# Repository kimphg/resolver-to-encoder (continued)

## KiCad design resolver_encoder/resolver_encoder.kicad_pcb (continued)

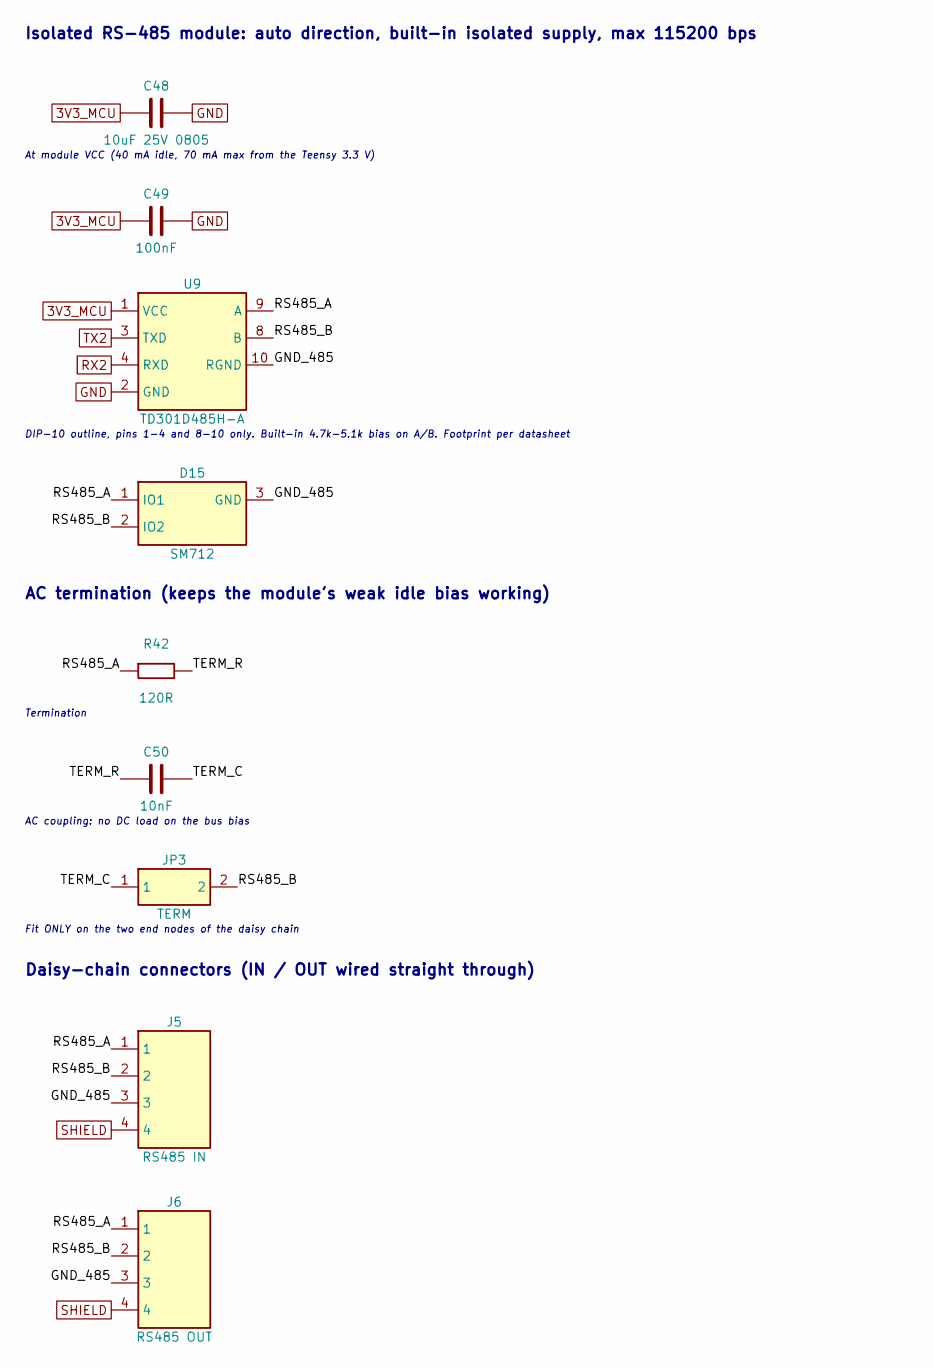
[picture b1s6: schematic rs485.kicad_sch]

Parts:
C48: 10uF 25V 0805; C_0805_2012Metric; MPN CL21A106KAYNNNE; LCSC C15850
C49: 100nF; C_0603_1608Metric; MPN CL10B104KB8NNNC; LCSC C1591
C50: 10nF; C_0603_1608Metric; MPN CL10B103KB8NNNC; LCSC C1589
D15: SM712; SOT-23; MPN SM712; LCSC C521963
J5: RS485 IN; PhoenixContact_MC_1,5_4-G-3.81_1x04_P3.81mm_Horizontal; MPN WJ15EDGRC-3.81-04P + plug WJ15EDGK-3.81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; LCSC C7245
J6: RS485 OUT; PhoenixContact_MC_1,5_4-G-3.81_1x04_P3.81mm_Horizontal; MPN WJ15EDGRC-3.81-04P + plug WJ15EDGK-3.81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; LCSC C7245
JP3: TERM; PinHeader_1x02_P2.54mm_Vertical; MPN 2.54 mm 1x40 header (cut) + jumper cap; LCSC C2337
R42: 120R; R_0805_2012Metric; MPN 0805W8F1200T5E; LCSC C17437
U9: TD301D485H-A; TD301D485H-A_DIP; MPN TD301D485H-A (YLPTEC); LCSC C2992416

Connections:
3V3_MCU: C48.1, C49.1, U9.1 (VCC); also elsewhere on the board
/RS485/GND_485: D15.3 (GND), J5.3, J6.3, U9.10 (RGND)
/RS485/RS485_A: D15.1 (IO1), J5.1, J6.1, R42.1, U9.9 (A)
/RS485/RS485_B: D15.2 (IO2), J5.2, J6.2, JP3.2, U9.8 (B)
/RS485/TERM_C: C50.2, JP3.1
/RS485/TERM_R: C50.1, R42.2
GND: C48.2, C49.2, U9.2 (GND); also elsewhere on the board
RX2: U9.4 (RXD); also elsewhere on the board
SHIELD: J5.4, J6.4; also elsewhere on the board
TX2: U9.3 (TXD); also elsewhere on the board

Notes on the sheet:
Isolated RS-485 module: auto direction, built-in isolated supply, max 115200 bps
At module VCC (40 mA idle, 70 mA max from the Teensy 3.3 V)
DIP-10 outline, pins 1-4 and 8-10 only. Built-in 4.7k-5.1k bias on A/B. Footprint per datasheet
AC termination (keeps the module's weak idle bias working)
Termination
AC coupling: no DC load on the bus bias
Fit ONLY on the two end nodes of the daisy chain
Daisy-chain connectors (IN / OUT wired straight through)

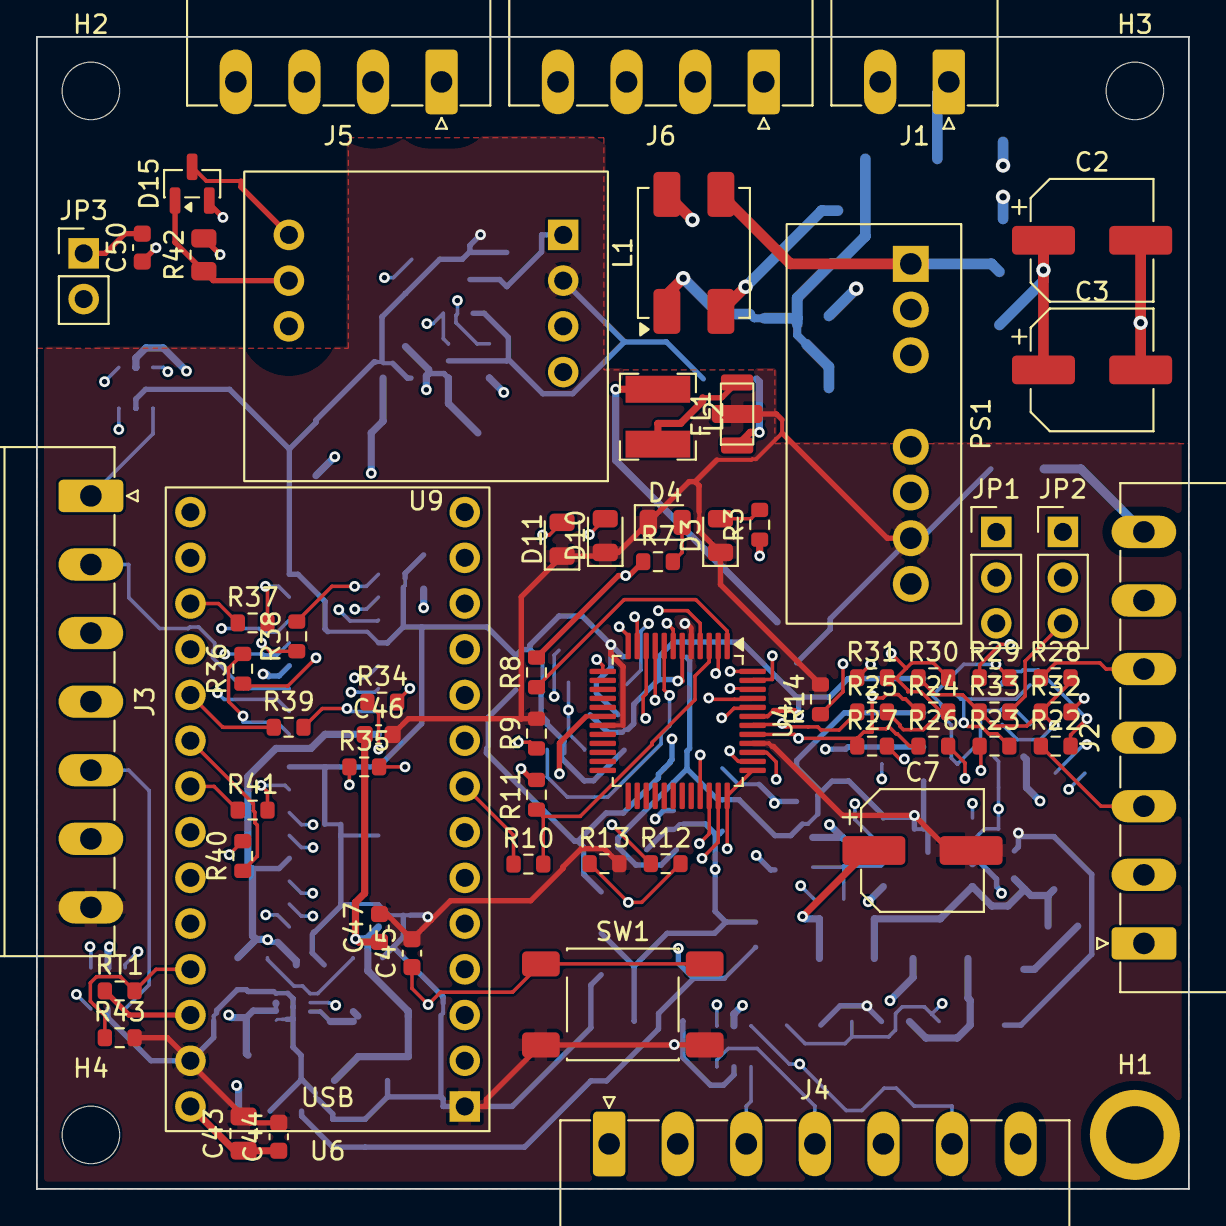
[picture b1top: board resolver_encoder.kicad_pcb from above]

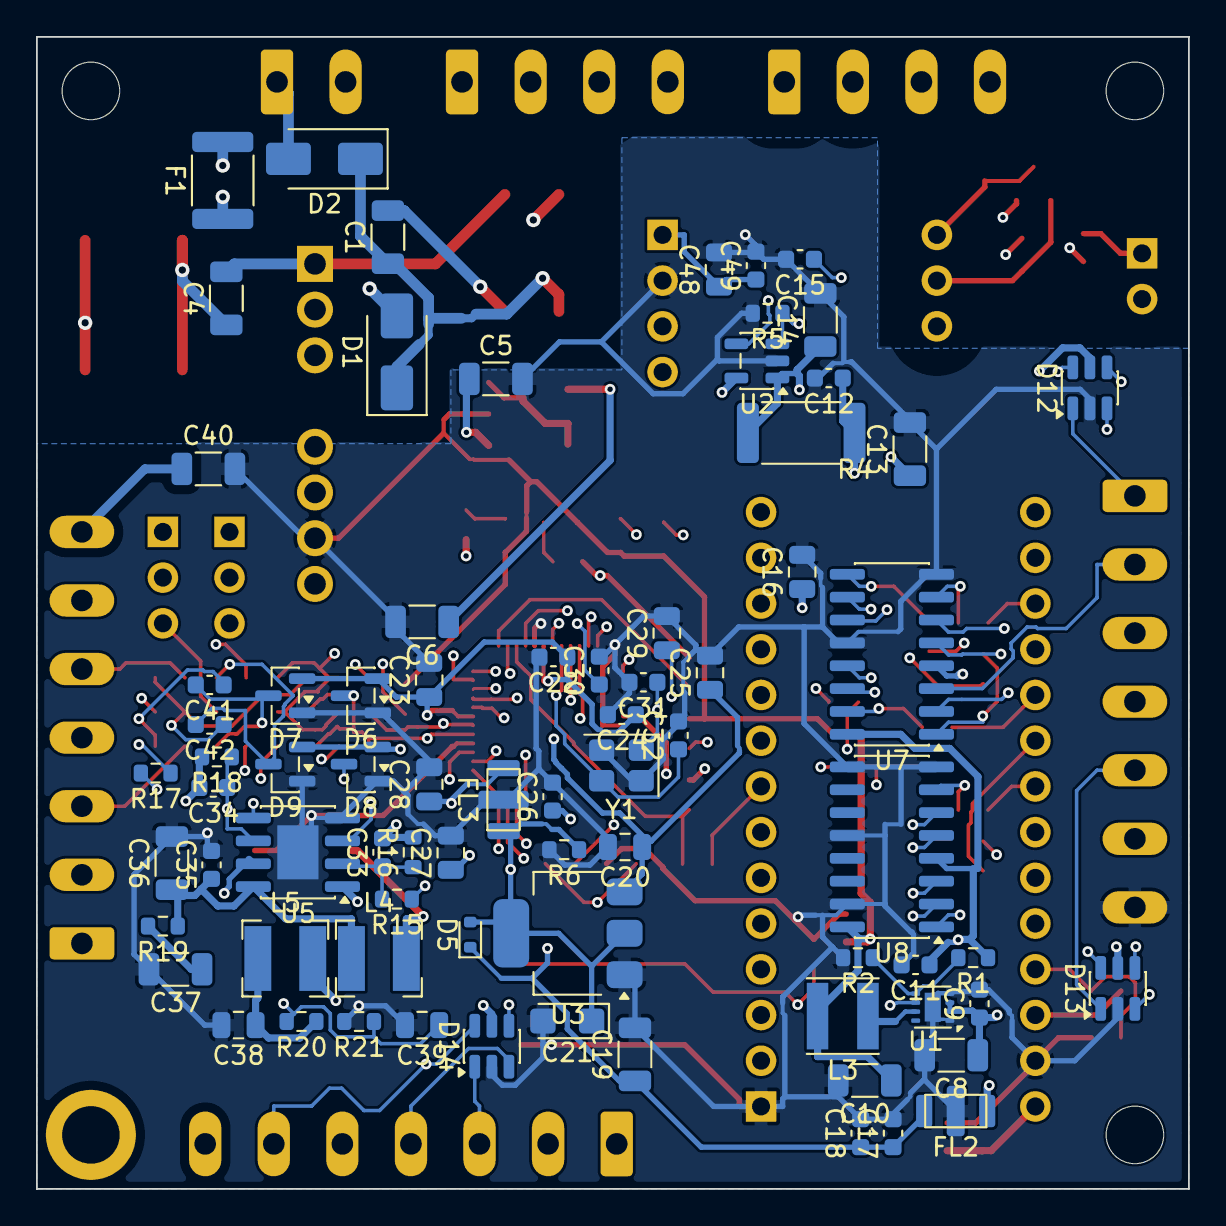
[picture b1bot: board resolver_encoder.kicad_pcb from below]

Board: 6 copper layers, 64.0 x 64.0 mm, 143 parts (76 on the bottom side), 102 nets.

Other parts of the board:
H2, H3, H4: M3 mounting hole; MountingHole_3.2mm_M3_ISO14580

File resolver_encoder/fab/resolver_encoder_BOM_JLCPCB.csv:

Comment,Designator,Footprint,LCSC Part #,MPN
2.2uF 50V,"C1,C4",C_1206_3216Metric,C50254,CL31B225KBHNNNE
47uF 50V,"C2,C3",CP_Elec_6.3x7.7,C72523,RVT1H470M0607
22uF 25V,"C5,C6,C8,C10,C14,C19,C37",C_1206_3216Metric,C12891,CL31A226KAHNNNE
47uF 25V,C7,CP_Elec_6.3x7.7,C136280,25SVPF47M
100nF,"C9,C11,C12,C17,C22,C24,C26,C35,C44,C45,C46,C47,C49",C_0603_1608Metric,C1591,CL10B104KB8NNNC
10uF 25V,"C13,C36",C_1206_3216Metric,C9807,CL31A106KAHNNNE
10nF,"C15,C30,C50",C_0603_1608Metric,C1589,CL10B103KB8NNNC
4.7uF 25V,"C16,C27,C39",C_0805_2012Metric,C1779,CL21A475KAQNNNE
22nF,C18,C_0603_1608Metric,C21122,CL10B223KB8NNNC
10uF 25V 0805,"C20,C23,C25,C29,C43,C48",C_0805_2012Metric,C15850,CL21A106KAYNNNE
22uF 10V tant,C21,CP_EIA-3216-18_Kemet-A,C11366,TAJA226K010RNJ
3.3uF 25V,"C28,C38",C_0805_2012Metric,C7393948,TCC0805X7R335K250FT
27pF C0G,"C31,C32",C_0603_1608Metric,C1656,CL10C270JB8NNNC
120pF C0G,"C33,C34",C_0603_1608Metric,C18438,CL10C121JB8NNNC
1nF 2kV,C40,C_1206_3216Metric,C23631,CC1206KKX7RDBB102
100pF C0G,"C41,C42",C_0603_1608Metric,C14858,CL10C101JB8NNNC
SS34,D1,D_SMA,C8678,SS34
SMAJ30A,D2,D_SMA,C353456,SMAJ30A
GREEN,"D3,D4,D10",LED_0805_2012Metric,C2297,KT-0805G
RB520S-30,D5,D_SOD-523,C8522,RB520S-30
BAT54S,"D6,D7,D8,D9",SOT-23,C916425,BAT54S
RED,D11,LED_0805_2012Metric,C84256,NCD0805R1
SRV05-4,"D12,D13,D14",SOT-23-6,C558418,SRV05-4
SM712,D15,SOT-23,C521963,SM712
PTC 0.5A 30V,F1,Fuse_1812_4532Metric,C12559,SMD1812P050TF/30
NFE31PT222Z1E9L,"FL1,FL2,FL3",Filter_Murata_NFE31PT_PROVISIONAL,C86146,NFE31PT222Z1E9L
24VDC IN,J1,"PhoenixContact_MC_1,5_2-G-3.81_1x02_P3.81mm_Horizontal",C8387,WJ15EDGRC-3.81-02P + plug WJ15EDGK-3.81-02P
RESOLVER,"J2,J3,J4","PhoenixContact_MC_1,5_7-G-3.81_1x07_P3.81mm_Horizontal",C24525,WJ15EDGRC-3.81-07P + plug WJ15EDGK-3.81-07P
RS485 IN,"J5,J6","PhoenixContact_MC_1,5_4-G-3.81_1x04_P3.81mm_Horizontal",C7245,WJ15EDGRC-3.81-04P + plug WJ15EDGK-3.81-04P
RATIO SIN,"JP1,JP2,JP3",PinHeader_1x03_P2.54mm_Vertical,C2337,2.54 mm 1x40 header (cut) + jumper cap
ACM7060-701-2PL,L1,L_CommonModeChoke_TDK_ACM7060,C78246,ACM7060-701-2PL-TL01
10uH,"L2,L4,L5",L_Bourns-SRN4018,C503307,SRN4018-100M
2.2uH,L3,L_Taiyo-Yuden_NR-40xx,C135262,SMNR4020-2.2UH
URB2412S-6WR3,PS1,URB_S-6WR3_SIP8,C3031186,URB2412S-6WR3 (YLPTEC)
105k 1%,R1,R_0603_1608Metric,C16840,0603WAF1053T5E
20k 1%,R2,R_0603_1608Metric,C4184,0603WAF2002T5E
1k,"R3,R9,R10,R12,R35",R_0603_1608Metric,C21190,0603WAF1001T5E
75R 1W,R4,R_2512_6332Metric,C25493,25121WJ0750T4E
100k,R5,R_0603_1608Metric,C25803,0603WAF1003T5E
470R,"R6,R7,R34",R_0603_1608Metric,C23179,0603WAF4700T5E
10k,"R8,R11,R13,R15,R17,R21",R_0603_1608Metric,C25804,0603WAF1002T5E
4.7k,R14,R_0603_1608Metric,C23162,0603WAF4701T5E
24.9k 1%,"R16,R18,R20",R_0603_1608Metric,C25962,0603WAF2492T5E
1R,R19,R_0603_1608Metric,C22936,0603WAF100KT5E
10.0k 0.1%,"R22,R23,R28,R29",R_0603_1608Metric,C95204,RT0603BRD0710KL
10.7k 0.1%,"R24,R25,R30,R31",R_0603_1608Metric,C2076333,ERA-3AEB1072V
51.1k 0.1%,"R26,R32",R_0603_1608Metric,C491138,ERA3AEB5112V
24.0k 0.1%,"R27,R33",R_0603_1608Metric,C326729,RT0603BRD0724KL
33R,"R36,R37,R38,R39,R40,R41",R_0603_1608Metric,C23140,0603WAF330JT5E
120R,R42,R_0805_2012Metric,C17437,0805W8F1200T5E
3.3k 1%,R43,R_0603_1608Metric,C22978,0603WAF3301T5E
10k NTC B3380,RT1,R_0603_1608Metric,C13564,NCP18XH103F03RB
CAL,SW1,SW_Push_1P1T_NO_E-Switch_TL3301NxxxxxG,C381064,TS-1102S-B-G-B
TPS62160DSGR,U1,WSON-8-1EP_2x2mm_P0.5mm_EP0.9x1.6mm,C324077,TPS62160DSGR
LP2985A-50DBVR,U2,SOT-23-5,C109382,LP2985A-50DBVR
AMS1117-3.3,U3,SOT-223-3_TabPin2,C6186,AMS1117-3.3
AD2S1210WDSTZ,U4,LQFP-48_7x7mm_P0.5mm,C443870,AD2S1210WDSTZ
AD8397ARDZ,U5,SOIC-8-1EP_3.9x4.9mm_P1.27mm_EP2.29x3mm,C578714,AD8397ARDZ
Teensy 4.0,U6,Teensy40_Sockets_2x14,C2905420,PJRC Teensy 4.0 (not on LCSC); sockets: 2 x KH-2.54FH-1X14P-H8.5
AM26C31IDR,"U7,U8",SOIC-16_3.9x9.9mm_P1.27mm,C34923,AM26C31IDR
TD301D485H-A,U9,TD301D485H-A_DIP,C2992416,TD301D485H-A (YLPTEC)
8MHz,Y1,Crystal_SMD_3225-4Pin_3.2x2.5mm,C2682774,X32258MSB4SI
